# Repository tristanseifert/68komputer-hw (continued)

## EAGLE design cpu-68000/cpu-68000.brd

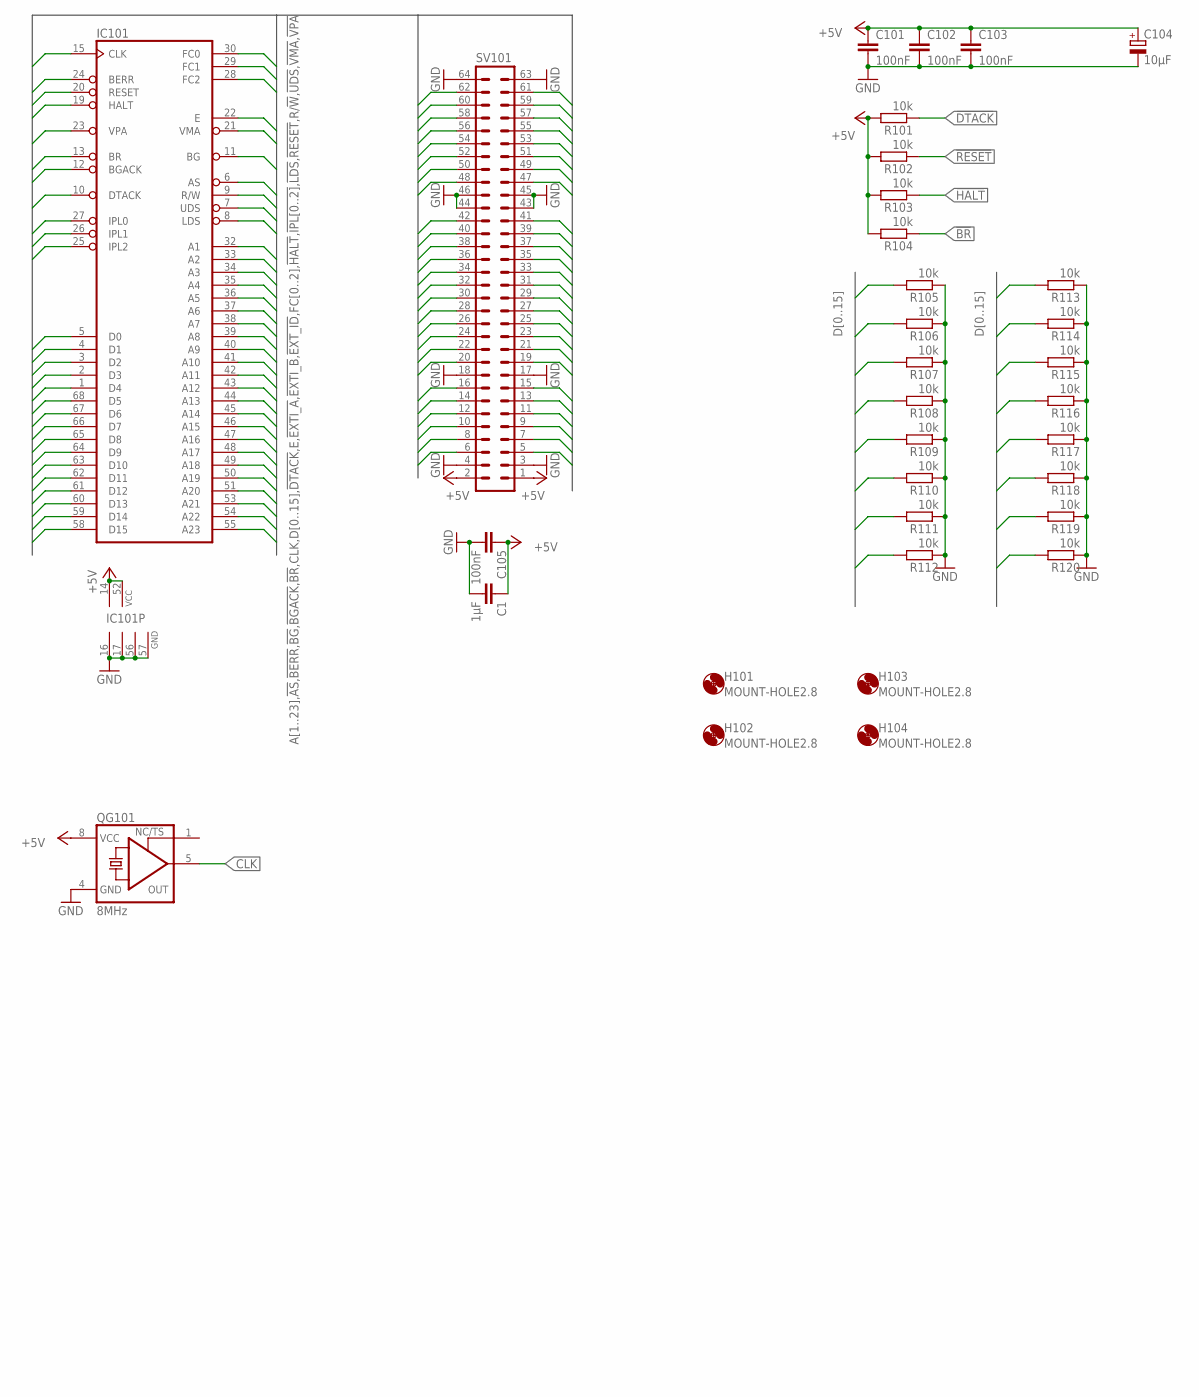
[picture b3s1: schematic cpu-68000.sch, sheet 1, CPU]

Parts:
C1: 1µF; C0805; MOUSER 710-885012207078
C101, C102, C103, C105: 100nF; C0805; MOUSER 710-885012207072
C104: 10µF; SMC_B; MOUSER 581-TAJB106K020RNJV
H101, H102, H103, H104: MOUNT-HOLE2.8; 2,8
IC101: MC68000FN-SOC; PLCC68SOCK; MOUSER_SOCKET 940-44-068-24-000000
QG101: 8MHz; DIL08S; MOUSER 774-MXO45HS-3C-8.0
R101, R102, R103, R104, R105, R106, R107, R108, R109, R110, R111, R112, R113, R114, R115, R116, R117, R118, R119, R120: 10k; R2012; MOUSER 652-CR0805FX-1002ELF
SV101: ML64L

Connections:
!AS: IC101.6 (AS), SV101.13; also elsewhere on the board
!BERR: IC101.24 (BERR); also elsewhere on the board
!BG: IC101.11 (BG), SV101.9
!BGACK: IC101.12 (BGACK), SV101.8
!BR: IC101.13 (BR), R104.1, SV101.7
!DTACK: IC101.10 (DTACK), R101.1, SV101.10; also elsewhere on the board
!EXTI_A: SV101.16; also elsewhere on the board
!EXTI_B: SV101.15; also elsewhere on the board
!EXT_ID: SV101.41; also elsewhere on the board
!HALT: IC101.19 (HALT), R103.1, SV101.5; also elsewhere on the board
!IPL0: IC101.27 (IPL0); also elsewhere on the board
!IPL1: IC101.26 (IPL1); also elsewhere on the board
!IPL2: IC101.25 (IPL2); also elsewhere on the board
!LDS: IC101.8 (LDS), SV101.11; also elsewhere on the board
!RESET: IC101.20 (RESET), R102.1, SV101.6; also elsewhere on the board
!UDS: IC101.7 (UDS), SV101.14; also elsewhere on the board
!VMA: IC101.21 (VMA)
!VPA: IC101.23 (VPA); also elsewhere on the board
+5V: C1.1, C101.1, C102.1, C103.1, C104.+, C105.1, IC101.14 (VCC), IC101.52 (VCC), QG101.8 (VCC), R101.2, R102.2, R103.2, R104.2, SV101.1, SV101.2; also elsewhere on the board
A1: IC101.32 (A1), SV101.20; also elsewhere on the board
A2: IC101.33 (A2), SV101.22; also elsewhere on the board
A3: IC101.34 (A3), SV101.19; also elsewhere on the board
A4: IC101.35 (A4), SV101.24; also elsewhere on the board
A5: IC101.36 (A5), SV101.21; also elsewhere on the board
A6: IC101.37 (A6), SV101.23; also elsewhere on the board
A7: IC101.38 (A7), SV101.26; also elsewhere on the board
A8: IC101.39 (A8), SV101.25; also elsewhere on the board
A9: IC101.40 (A9), SV101.28; also elsewhere on the board
A10: IC101.41 (A10), SV101.27; also elsewhere on the board
A11: IC101.42 (A11), SV101.30; also elsewhere on the board
A12: IC101.43 (A12), SV101.29; also elsewhere on the board
A13: IC101.44 (A13), SV101.31; also elsewhere on the board
A14: IC101.45 (A14), SV101.32; also elsewhere on the board
A15: IC101.46 (A15), SV101.33; also elsewhere on the board
A16: IC101.47 (A16), SV101.34; also elsewhere on the board
A17: IC101.48 (A17), SV101.36; also elsewhere on the board
A18: IC101.49 (A18), SV101.35; also elsewhere on the board
A19: IC101.50 (A19), SV101.38; also elsewhere on the board
A20: IC101.51 (A20), SV101.37; also elsewhere on the board
A21: IC101.53 (A21), SV101.40; also elsewhere on the board
A22: IC101.54 (A22), SV101.39; also elsewhere on the board
A23: IC101.55 (A23), SV101.42; also elsewhere on the board
CLK: IC101.15 (CLK), QG101.5 (OUT); also elsewhere on the board
D0: IC101.5 (D0), R105.2, SV101.62; also elsewhere on the board
D1: IC101.4 (D1), R106.2, SV101.60; also elsewhere on the board
D2: IC101.3 (D2), R107.2, SV101.58; also elsewhere on the board
D3: IC101.2 (D3), R108.2, SV101.56; also elsewhere on the board
D4: IC101.1 (D4), R109.2, SV101.54; also elsewhere on the board
D5: IC101.68 (D5), R110.2, SV101.52; also elsewhere on the board
D6: IC101.67 (D6), R111.2, SV101.50; also elsewhere on the board
D7: IC101.66 (D7), R112.2, SV101.48; also elsewhere on the board
D8: IC101.65 (D8), R113.2, SV101.57; also elsewhere on the board
D9: IC101.64 (D9), R114.2, SV101.59; also elsewhere on the board
D10: IC101.63 (D10), R115.2, SV101.61; also elsewhere on the board
D11: IC101.62 (D11), R116.2, SV101.55; also elsewhere on the board
D12: IC101.61 (D12), R117.2, SV101.53; also elsewhere on the board
D13: IC101.60 (D13), R118.2, SV101.51; also elsewhere on the board
D14: IC101.59 (D14), R119.2, SV101.49; also elsewhere on the board
D15: IC101.58 (D15), R120.2, SV101.47; also elsewhere on the board
E: IC101.22 (E); also elsewhere on the board
FC0: IC101.30 (FC0); also elsewhere on the board
FC1: IC101.29 (FC1); also elsewhere on the board
FC2: IC101.28 (FC2); also elsewhere on the board
GND: C1.2, C101.2, C102.2, C103.2, C104.-, C105.2, IC101.16 (GND), IC101.17 (GND), IC101.56 (GND), IC101.57 (GND), QG101.4 (GND), R105.1, R106.1, R107.1, R108.1, R109.1, R110.1, R111.1, R112.1, R113.1, R114.1, R115.1, R116.1, R117.1, R118.1, R119.1, R120.1, SV101.3, SV101.4, SV101.17, SV101.18, SV101.43, SV101.44, SV101.45, SV101.46, SV101.63, SV101.64; also elsewhere on the board
R/!W!: IC101.9 (R/W), SV101.12; also elsewhere on the board

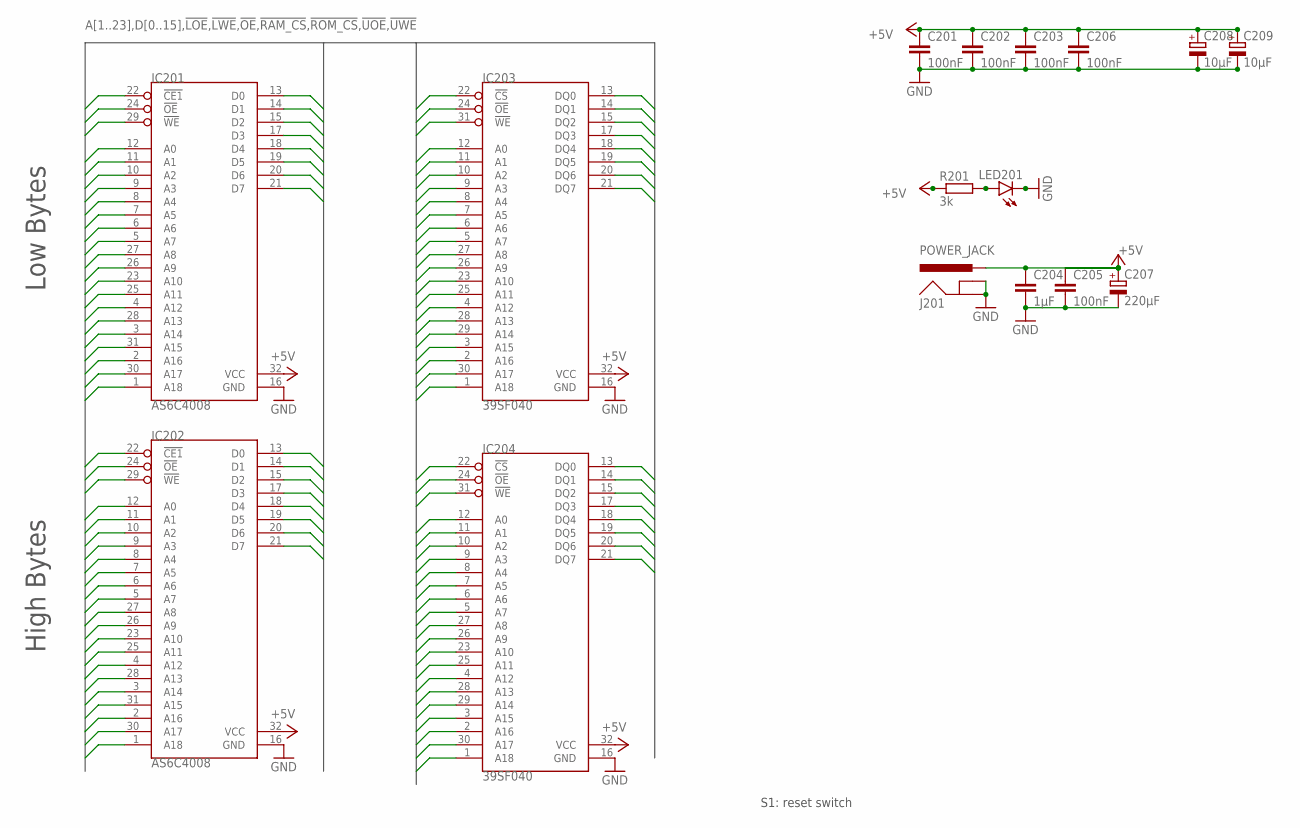
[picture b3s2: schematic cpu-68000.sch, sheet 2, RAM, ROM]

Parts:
C201, C202, C203, C205, C206: 100nF; C0805; MOUSER 710-885012207072
C204: 1µF; C0805; MOUSER 710-885012107015
C207: 220µF; E2,5-7; MOUSER 710-860020373010
C208, C209: 10µF; SMC_B; MOUSER 581-TAJB106K020RNJV
IC201, IC202: AS6C4008; DIL32; MOUSER_SOCKET 575-1144632
IC203, IC204: 39SF040; DIL32; MOUSER 804-39SF0407CPHE
J201: POWER_JACK; POWER_JACK_PTH
LED201: LEDCHIPLED_1206; CHIPLED_1206; MOUSER 710-156120YS75300
R201: 3k; R2012; MOUSER 652-CR0805JW-302ELF

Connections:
!LOE: IC201.24 (!OE), IC203.24 (!OE); also elsewhere on the board
!LWE: IC201.29 (!WE), IC203.31 (!WE); also elsewhere on the board
!RAM_CS: IC201.22 (!CE1), IC202.22 (!CE1); also elsewhere on the board
!ROM_CS: IC203.22 (!CS), IC204.22 (!CS); also elsewhere on the board
!UOE: IC202.24 (!OE), IC204.24 (!OE); also elsewhere on the board
!UWE: IC202.29 (!WE), IC204.31 (!WE); also elsewhere on the board
+5V: C201.1, C202.1, C203.1, C204.1, C205.1, C206.1, C207.+, C208.+, C209.+, IC201.32 (VCC), IC202.32 (VCC), IC203.32 (VCC), IC204.32 (VCC), J201.PWR, R201.1; also elsewhere on the board
A1: IC201.12 (A0), IC202.12 (A0), IC203.12 (A0), IC204.12 (A0); also elsewhere on the board
A2: IC201.11 (A1), IC202.11 (A1), IC203.11 (A1), IC204.11 (A1); also elsewhere on the board
A3: IC201.10 (A2), IC202.10 (A2), IC203.10 (A2), IC204.10 (A2); also elsewhere on the board
A4: IC201.9 (A3), IC202.9 (A3), IC203.9 (A3), IC204.9 (A3); also elsewhere on the board
A5: IC201.8 (A4), IC202.8 (A4), IC203.8 (A4), IC204.8 (A4); also elsewhere on the board
A6: IC201.7 (A5), IC202.7 (A5), IC203.7 (A5), IC204.7 (A5); also elsewhere on the board
A7: IC201.6 (A6), IC202.6 (A6), IC203.6 (A6), IC204.6 (A6); also elsewhere on the board
A8: IC201.5 (A7), IC202.5 (A7), IC203.5 (A7), IC204.5 (A7); also elsewhere on the board
A9: IC201.27 (A8), IC202.27 (A8), IC203.27 (A8), IC204.27 (A8); also elsewhere on the board
A10: IC201.26 (A9), IC202.26 (A9), IC203.26 (A9), IC204.26 (A9); also elsewhere on the board
A11: IC201.23 (A10), IC202.23 (A10), IC203.23 (A10), IC204.23 (A10); also elsewhere on the board
A12: IC201.25 (A11), IC202.25 (A11), IC203.25 (A11), IC204.25 (A11); also elsewhere on the board
A13: IC201.4 (A12), IC202.4 (A12), IC203.4 (A12), IC204.4 (A12); also elsewhere on the board
A14: IC201.28 (A13), IC202.28 (A13), IC203.28 (A13), IC204.28 (A13); also elsewhere on the board
A15: IC201.3 (A14), IC202.3 (A14), IC203.29 (A14), IC204.29 (A14); also elsewhere on the board
A16: IC201.31 (A15), IC202.31 (A15), IC203.3 (A15), IC204.3 (A15); also elsewhere on the board
A17: IC201.2 (A16), IC202.2 (A16), IC203.2 (A16), IC204.2 (A16); also elsewhere on the board
A18: IC201.30 (A17), IC202.30 (A17), IC203.30 (A17), IC204.30 (A17); also elsewhere on the board
A19: IC201.1 (A18), IC202.1 (A18), IC203.1 (A18), IC204.1 (A18); also elsewhere on the board
D0: IC201.13 (D0), IC203.13 (DQ0); also elsewhere on the board
D1: IC201.14 (D1), IC203.14 (DQ1); also elsewhere on the board
D2: IC201.15 (D2), IC203.15 (DQ2); also elsewhere on the board
D3: IC201.17 (D3), IC203.17 (DQ3); also elsewhere on the board
D4: IC201.18 (D4), IC203.18 (DQ4); also elsewhere on the board
D5: IC201.19 (D5), IC203.19 (DQ5); also elsewhere on the board
D6: IC201.20 (D6), IC203.20 (DQ6); also elsewhere on the board
D7: IC201.21 (D7), IC203.21 (DQ7); also elsewhere on the board
D8: IC202.13 (D0), IC204.13 (DQ0); also elsewhere on the board
D9: IC202.14 (D1), IC204.14 (DQ1); also elsewhere on the board
D10: IC202.15 (D2), IC204.15 (DQ2); also elsewhere on the board
D11: IC202.17 (D3), IC204.17 (DQ3); also elsewhere on the board
D12: IC202.18 (D4), IC204.18 (DQ4); also elsewhere on the board
D13: IC202.19 (D5), IC204.19 (DQ5); also elsewhere on the board
D14: IC202.20 (D6), IC204.20 (DQ6); also elsewhere on the board
D15: IC202.21 (D7), IC204.21 (DQ7); also elsewhere on the board
GND: C201.2, C202.2, C203.2, C204.2, C205.2, C206.2, C207.-, C208.-, C209.-, IC201.16 (GND), IC202.16 (GND), IC203.16 (GND), IC204.16 (GND), J201.GND, J201.GNDBREAK, LED201.C; also elsewhere on the board
unnamed: LED201.A, R201.2

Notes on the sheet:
S1: reset switch
Low Bytes
High Bytes

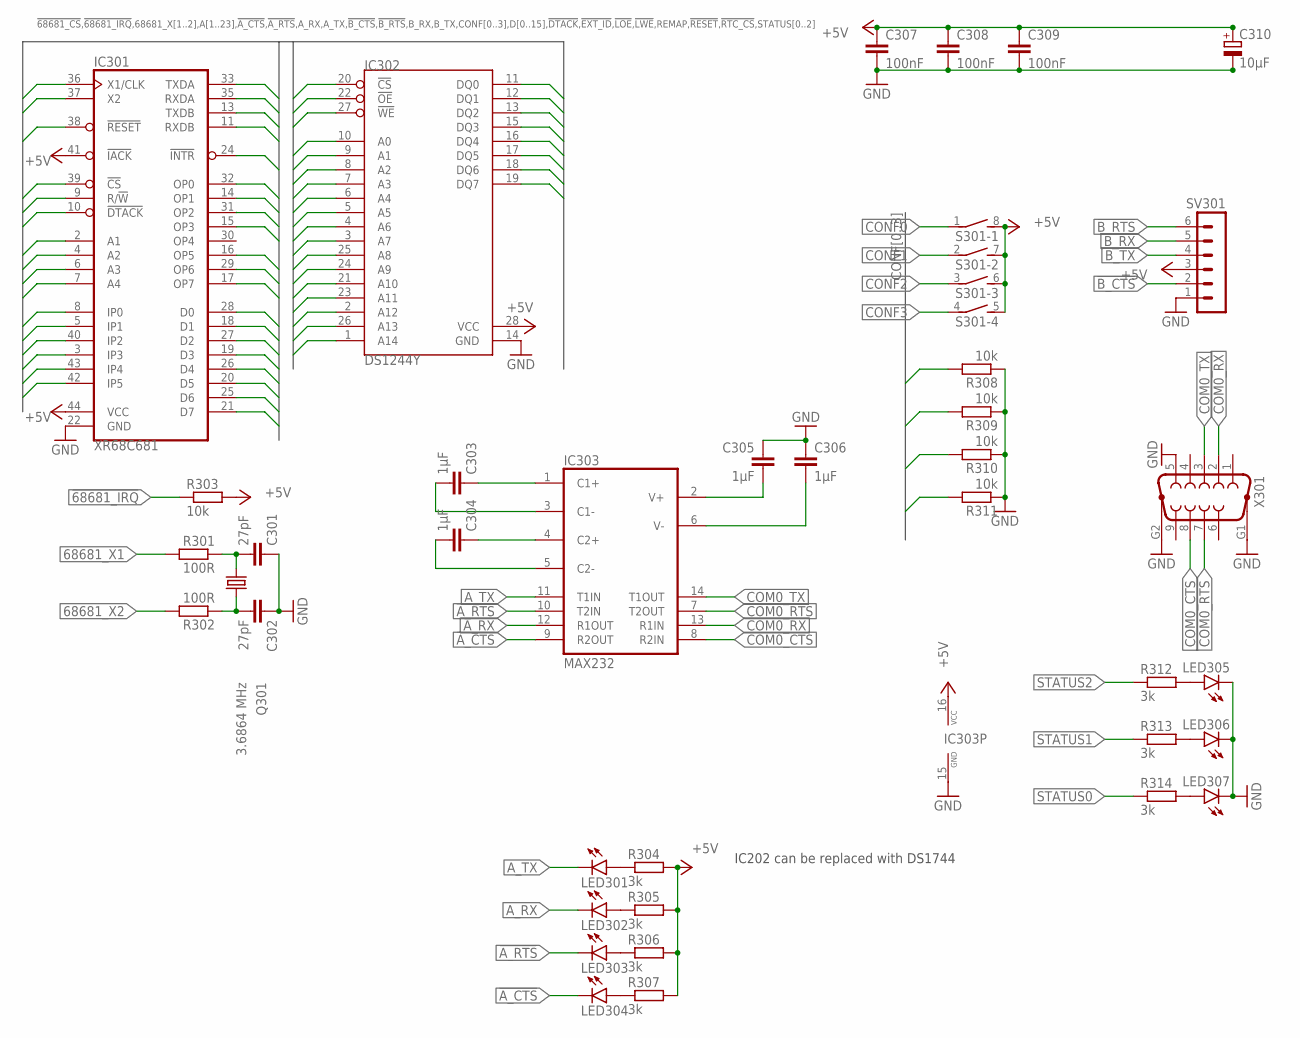
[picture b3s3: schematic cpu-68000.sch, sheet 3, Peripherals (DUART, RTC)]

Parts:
C301, C302: 27pF; C0805; MOUSER 80-C0805C270K5HACTU
C303, C304, C305, C306: 1µF; C0805; MOUSER 710-885012207078
C307, C308, C309: 100nF; C0805; MOUSER 710-885012207072
C310: 10µF; SMC_B; MOUSER 581-TAJB106K020RNJV
IC301: XR68C681; PLCC-S44; MOUSER 701-XR68C681CJ-F
IC302: DS1244Y; DIL28-6; MOUSER_SOCKET 575-1104762841001000
IC303: MAX232; DIL16; MOUSER 595-MAX232ECN
LED301, LED302, LED303, LED304, LED305, LED306, LED307: LEDCHIPLED_1206; CHIPLED_1206; MOUSER 710-156120VS75300
Q301: 3.6864 MHz; HC49/S; MOUSER 815-ABL-3.6864-B2
R301, R302: 100R; R2012; MOUSER 652-CR0805FX-1000ELF
R303, R308, R309, R310, R311: 10k; R2012; MOUSER 652-CR0805FX-1002ELF
R304, R305, R306, R307, R312, R313, R314: 3k; R2012; MOUSER 652-CR0805JW-302ELF
S301: DIP04S; MOUSER 653-A6FR-4104
SV301: MA06-1
X301: F09HP; MOUSER 806-K22X-E9P-N-99

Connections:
68681_X1: IC301.36 (X1/CLK), R301.2
68681_X2: IC301.37 (X2), R302.2
!68681_CS: IC301.39 (!CS); also elsewhere on the board
!68681_IRQ: IC301.24 (!INTR), R303.1; also elsewhere on the board
!A_CTS: IC301.8 (IP0), IC303.9 (R2OUT), LED304.C
!A_RTS: IC301.32 (OP0), IC303.10 (T2IN), LED303.C
!B_CTS: IC301.5 (IP1), SV301.2
!B_RTS: IC301.14 (OP1), SV301.6
!DTACK: IC301.10 (!DTACK); also elsewhere on the board
!EXT_ID: IC301.29 (OP6); also elsewhere on the board
!LOE: IC302.22 (!OE); also elsewhere on the board
!LWE: IC301.9 (R/!W), IC302.27 (!WE); also elsewhere on the board
!RESET: IC301.38 (!RESET); also elsewhere on the board
!RTC_CS: IC302.20 (!CS); also elsewhere on the board
+5V: C307.1, C308.1, C309.1, C310.+, IC301.41 (!IACK), IC301.44 (VCC), IC302.28 (VCC), IC303.16 (VCC), R303.2, R304.2, R305.2, R306.2, R307.2, S301.5 (2), S301.6 (2), S301.7 (2), S301.8 (2), SV301.3; also elsewhere on the board
A1: IC301.2 (A1), IC302.10 (A0); also elsewhere on the board
A2: IC301.4 (A2), IC302.9 (A1); also elsewhere on the board
A3: IC301.6 (A3), IC302.8 (A2); also elsewhere on the board
A4: IC301.7 (A4), IC302.7 (A3); also elsewhere on the board
A5: IC302.6 (A4); also elsewhere on the board
A6: IC302.5 (A5); also elsewhere on the board
A7: IC302.4 (A6); also elsewhere on the board
A8: IC302.3 (A7); also elsewhere on the board
A9: IC302.25 (A8); also elsewhere on the board
A10: IC302.24 (A9); also elsewhere on the board
A11: IC302.21 (A10); also elsewhere on the board
A12: IC302.23 (A11); also elsewhere on the board
A13: IC302.2 (A12); also elsewhere on the board
A14: IC302.26 (A13); also elsewhere on the board
A15: IC302.1 (A14); also elsewhere on the board
A_RX: IC301.35 (RXDA), IC303.12 (R1OUT), LED302.C
A_TX: IC301.33 (TXDA), IC303.11 (T1IN), LED301.C
B_RX: IC301.11 (RXDB), SV301.5
B_TX: IC301.13 (TXDB), SV301.4
COM0_CTS: IC303.8 (R2IN), X301.8
COM0_RTS: IC303.7 (T2OUT), X301.7
COM0_RX: IC303.13 (R1IN), X301.2
COM0_TX: IC303.14 (T1OUT), X301.3
CONF0: IC301.40 (IP2), R308.2, S301.1
CONF1: IC301.43 (IP4), R309.2, S301.2 (1)
CONF2: IC301.42 (IP5), R310.2, S301.3 (1)
CONF3: IC301.3 (IP3), R311.2, S301.4 (1)
D0: IC301.28 (D0), IC302.11 (DQ0); also elsewhere on the board
D1: IC301.18 (D1), IC302.12 (DQ1); also elsewhere on the board
D2: IC301.27 (D2), IC302.13 (DQ2); also elsewhere on the board
D3: IC301.19 (D3), IC302.15 (DQ3); also elsewhere on the board
D4: IC301.26 (D4), IC302.16 (DQ4); also elsewhere on the board
D5: IC301.20 (D5), IC302.17 (DQ5); also elsewhere on the board
D6: IC301.25 (D6), IC302.18 (DQ6); also elsewhere on the board
D7: IC301.21 (D7), IC302.19 (DQ7); also elsewhere on the board
GND: C301.1, C302.1, C305.1, C306.1, C307.2, C308.2, C309.2, C310.-, IC301.22 (GND), IC302.14 (GND), IC303.15 (GND), LED305.C, LED306.C, LED307.C, R308.1, R309.1, R310.1, R311.1, SV301.1, X301.5, X301.G1, X301.G2; also elsewhere on the board
unnamed: C305.2, IC303.2 (V+)
unnamed: C301.2, Q301.1, R301.1
unnamed: C302.2, Q301.2, R302.1
unnamed: LED306.A, R313.2
unnamed: LED307.A, R314.2
unnamed: LED305.A, R312.2
unnamed: LED301.A, R304.1
unnamed: LED302.A, R305.1
unnamed: LED303.A, R306.1
unnamed: LED304.A, R307.1
unnamed: C306.2, IC303.6 (V-)
unnamed: C304.1, IC303.4 (C2+)
unnamed: C303.1, IC303.1 (C1+)
unnamed: C303.2, IC303.3 (C1-)
unnamed: C304.2, IC303.5 (C2-)
REMAP: IC301.31 (OP2); also elsewhere on the board
STATUS0: IC301.16 (OP5), R314.1
STATUS1: IC301.17 (OP7), R313.1
STATUS2: IC301.15 (OP3), R312.1

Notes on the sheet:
IC202 can be replaced with DS1744

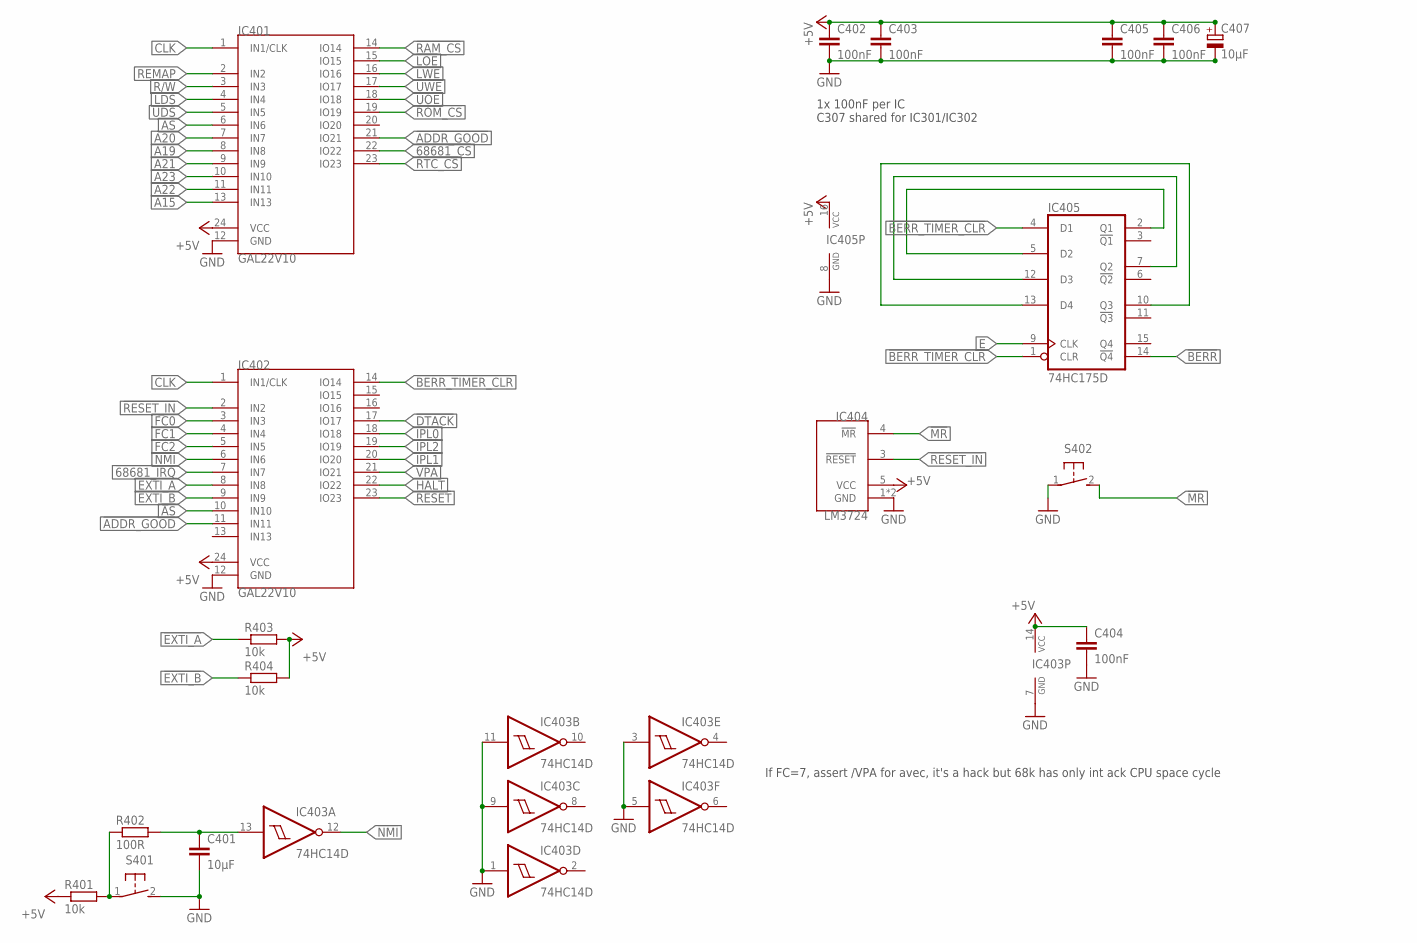
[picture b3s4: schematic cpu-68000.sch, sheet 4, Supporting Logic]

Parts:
C401: 10µF; C0805; MOUSER 791-0805F106Z100CT
C402, C403, C404, C405, C406: 100nF; C0805; MOUSER 710-885012207072
C407: 10µF; SMC_B; MOUSER 581-TAJB106K020RNJV
IC401, IC402: GAL22V10; DIL24S; MOUSER_SOCKET 575-1104732441001000
IC403: 74HC14D; SO14; MOUSER 771-74HC14D-T
IC404: LM3724; SOT23-5
IC405: 74HC175D; SO16; MOUSER 595-CD74HCT175M
R401, R403, R404: 10k; R2012; MOUSER 652-CR0805FX-1002ELF
R402: 100R; R2012; MOUSER 652-CR0805JW-101ELF
S401, S402: 31-XX; B3F-31XX; MOUSER 653-B3F-3150

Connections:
!68681_CS: IC401.22 (IO22); also elsewhere on the board
!68681_IRQ: IC402.7 (IN7); also elsewhere on the board
!ADDR_GOOD: IC401.21 (IO21), IC402.11 (IN11)
!AS: IC401.6 (IN6), IC402.10 (IN10); also elsewhere on the board
!BERR: IC405.14 (!Q4); also elsewhere on the board
!BERR_TIMER_CLR: IC402.14 (IO14), IC405.1 (CLR), IC405.4 (D1)
!DTACK: IC402.17 (IO17); also elsewhere on the board
!EXTI_A: IC402.8 (IN8), R403.1; also elsewhere on the board
!EXTI_B: IC402.9 (IN9), R404.1; also elsewhere on the board
!HALT: IC402.22 (IO22); also elsewhere on the board
!IPL0: IC402.18 (IO18); also elsewhere on the board
!IPL1: IC402.20 (IO20); also elsewhere on the board
!IPL2: IC402.19 (IO19); also elsewhere on the board
!LDS: IC401.4 (IN4); also elsewhere on the board
!LOE: IC401.15 (IO15); also elsewhere on the board
!LWE: IC401.16 (IO16); also elsewhere on the board
!MR: IC404.4 (!MR), S402.2 (S)
!NMI: IC402.6 (IN6), IC403.12 (O)
!RAM_CS: IC401.14 (IO14); also elsewhere on the board
!RESET: IC402.23 (IO23); also elsewhere on the board
!RESET_IN: IC402.2 (IN2), IC404.3 (!RESET)
!ROM_CS: IC401.19 (IO19); also elsewhere on the board
!RTC_CS: IC401.23 (IO23); also elsewhere on the board
!UDS: IC401.5 (IN5); also elsewhere on the board
!UOE: IC401.18 (IO18); also elsewhere on the board
!UWE: IC401.17 (IO17); also elsewhere on the board
!VPA: IC402.21 (IO21); also elsewhere on the board
+5V: C402.1, C403.1, C404.1, C405.1, C406.1, C407.+, IC401.24 (VCC), IC402.24 (VCC), IC403.14 (VCC), IC404.5 (VCC), IC405.16 (VCC), R401.1, R403.2, R404.2; also elsewhere on the board
A15: IC401.13 (IN13); also elsewhere on the board
A19: IC401.8 (IN8); also elsewhere on the board
A20: IC401.7 (IN7); also elsewhere on the board
A21: IC401.9 (IN9); also elsewhere on the board
A22: IC401.11 (IN11); also elsewhere on the board
A23: IC401.10 (IN10); also elsewhere on the board
CLK: IC401.1 (IN1/CLK), IC402.1 (IN1/CLK); also elsewhere on the board
E: IC405.9 (CLK); also elsewhere on the board
FC0: IC402.3 (IN3); also elsewhere on the board
FC1: IC402.4 (IN4); also elsewhere on the board
FC2: IC402.5 (IN5); also elsewhere on the board
GND: C401.2, C402.2, C403.2, C404.2, C405.2, C406.2, C407.-, IC401.12 (GND), IC402.12 (GND), IC403.1 (I), IC403.3 (I), IC403.5 (I), IC403.7 (GND), IC403.9 (I), IC403.11 (I), IC404.1 (GND), IC404.2 (GND), IC405.8 (GND), S401.2 (S), S402.1; also elsewhere on the board
unnamed: IC405.2 (Q1), IC405.5 (D2)
unnamed: IC405.7 (Q2), IC405.12 (D3)
unnamed: IC405.10 (Q3), IC405.13 (D4)
unnamed: R401.2, R402.1, S401.1
unnamed: C401.1, IC403.13 (I), R402.2
R/!W!: IC401.3 (IN3); also elsewhere on the board
REMAP: IC401.2 (IN2); also elsewhere on the board

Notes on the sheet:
1x 100nF per IC C307 shared for IC301/IC302
If FC=7, assert /VPA for avec, it's a hack but 68k has only int ack CPU space cycle

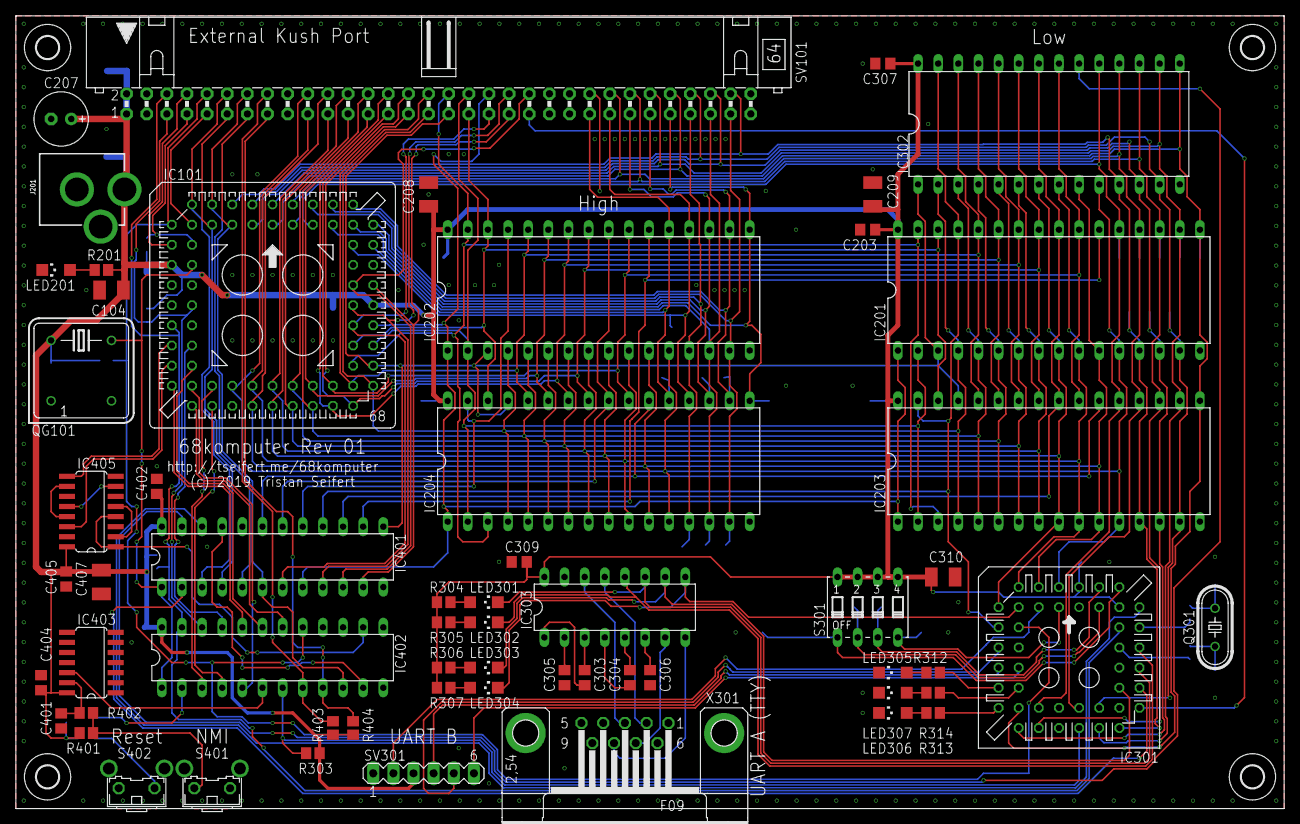
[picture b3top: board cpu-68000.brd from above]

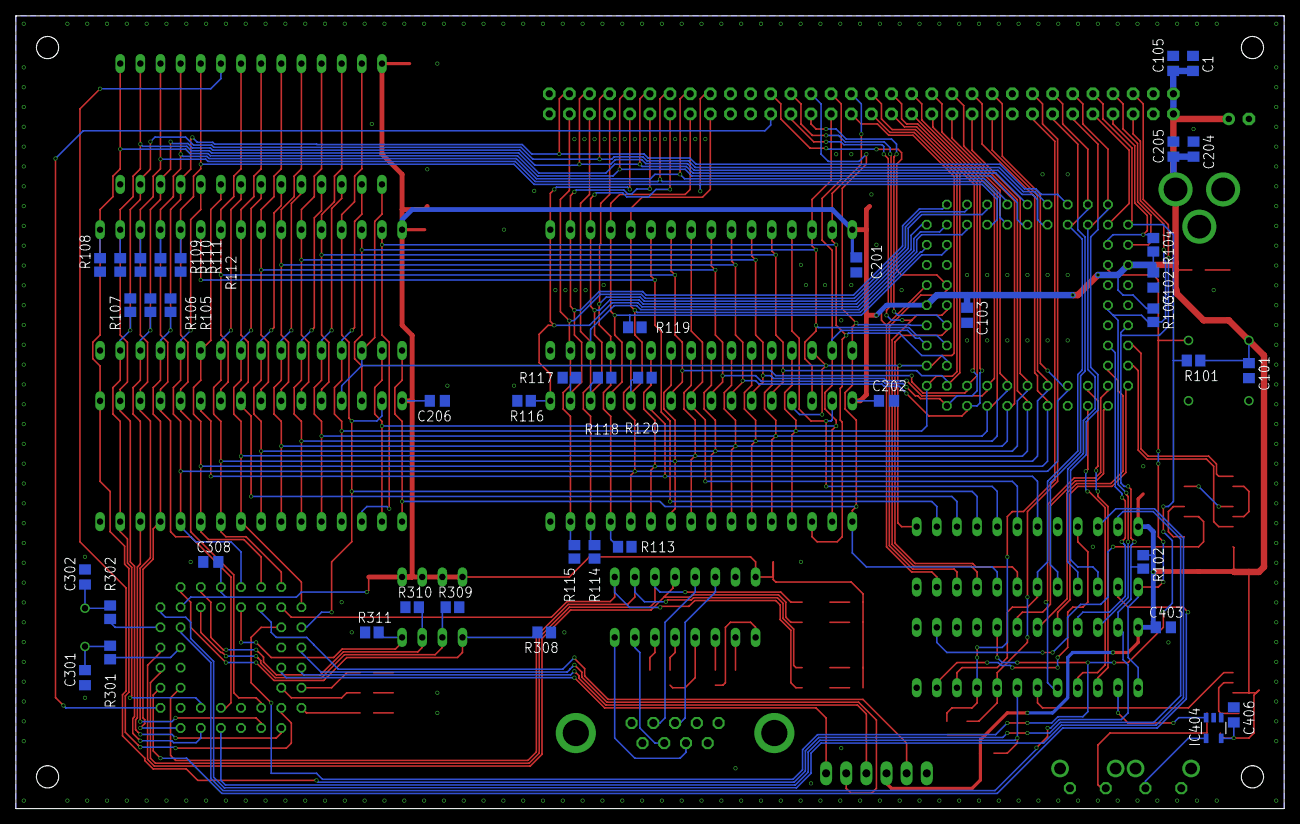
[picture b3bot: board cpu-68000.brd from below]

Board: 2 copper layers, 160.0 x 100.0 mm, 105 parts (42 on the bottom side), 121 nets.

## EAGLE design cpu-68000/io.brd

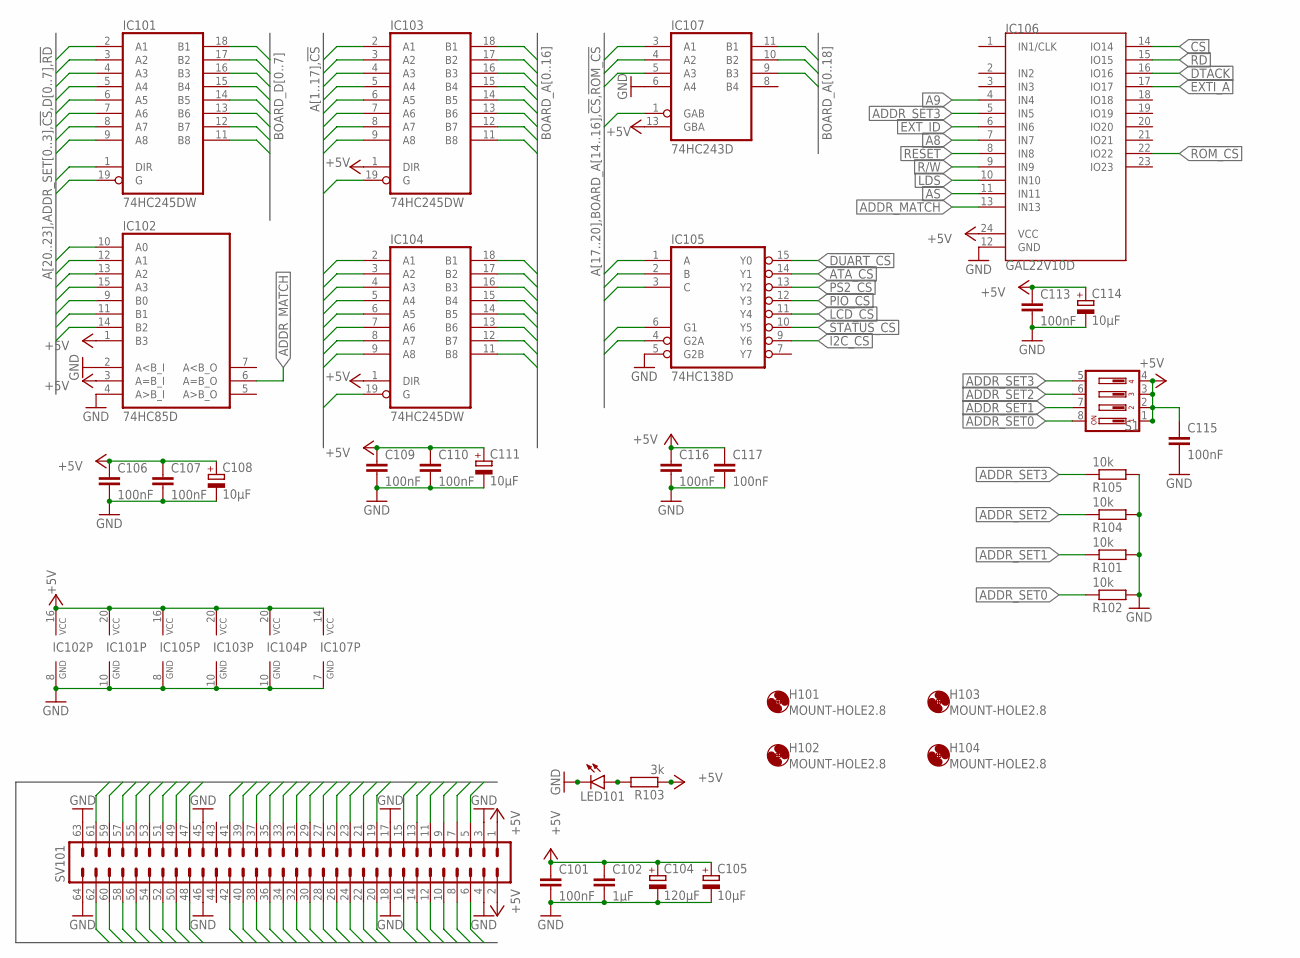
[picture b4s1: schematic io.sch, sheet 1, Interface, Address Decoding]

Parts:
C101, C106, C107, C109, C110, C113, C115, C116, C117: 100nF; C0805; MOUSER 710-885012207072
C102: 1µF; C0805; MOUSER 710-885012207078
C104: 120µF; E2,5-7; MOUSER 710-860020373007
C105, C108, C111, C114: 10µF; SMC_B; MOUSER 581-TAJB106K020RNJV
H101, H102, H103, H104: MOUNT-HOLE2.8; 2,8
IC101, IC103, IC104: 74HC245DW; SO20W; MOUSER 595-SN74HC245DWR
IC102: 74HC85D; SO16; MOUSER 771-74HC138D
IC105: 74HC138D; SO16; MOUSER 771-74HC138D
IC106: GAL22V10D; DIL24S; MOUSER_SOCKET 575-1104732441001000
IC107: 74HC243D; SO14; MOUSER 595-CD74HC243M96
LED101: LEDCHIPLED_1206; CHIPLED_1206; MOUSER 710-156120YS75300
R101, R102, R104, R105: 10k; R2012; MOUSER 652-CR0805FX-1002ELF
R103: 3k; R2012; MOUSER 652-CR0805JW-302ELF
S1: DP04; DP-04; MOUSER 653-A6FR-2104
SV101: ML64L

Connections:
!AS: IC106.11 (IN11), SV101.13
!ATA_CS: IC105.14 (Y1)
!BG: SV101.9
!BGACK: SV101.8
!BR: SV101.7
!CS: IC101.19 (G), IC103.19 (G), IC104.19 (G), IC105.4 (G2A), IC106.14 (IO14), IC107.1 (GAB)
!DTACK: IC106.16 (IO16), SV101.10; also elsewhere on the board
!DUART_CS: IC105.15 (Y0); also elsewhere on the board
!EXTI_A: IC106.17 (IO17), SV101.16
!EXTI_B: SV101.15
!EXT_ID: IC106.6 (IN6), SV101.41
!HALT: SV101.5
!I2C_CS: IC105.9 (Y6)
!LCD_CS: IC105.11 (Y4)
!LDS: IC106.10 (IN10), SV101.11
!PIO_CS: IC105.12 (Y3)
!PS2_CS: IC105.13 (Y2); also elsewhere on the board
!RD: IC101.1 (DIR), IC106.15 (IO15); also elsewhere on the board
!RESET: IC106.8 (IN8), SV101.6; also elsewhere on the board
!ROM_CS: IC105.6 (G1), IC106.22 (IO22); also elsewhere on the board
!STATUS_CS: IC105.10 (Y5)
!UDS: SV101.14
+5V: C101.1, C102.1, C104.+, C105.+, C106.1, C107.1, C108.+, C109.1, C110.1, C111.+, C113.1, C114.+, C115.1, C116.1, C117.1, IC101.20 (VCC), IC102.1 (B3), IC102.3 (A=B_I), IC102.16 (VCC), IC103.1 (DIR), IC103.20 (VCC), IC104.1 (DIR), IC104.20 (VCC), IC105.16 (VCC), IC106.24 (VCC), IC107.13 (GBA), IC107.14 (VCC), R103.1, S1.1, S1.2, S1.3, S1.4, SV101.1, SV101.2; also elsewhere on the board
A1: IC103.2 (A1), SV101.20
A2: IC103.3 (A2), SV101.22
A3: IC103.4 (A3), SV101.19
A4: IC103.5 (A4), SV101.24
A5: IC103.6 (A5), SV101.21
A6: IC103.7 (A6), SV101.23
A7: IC103.8 (A7), SV101.26
A8: IC103.9 (A8), IC106.7 (IN7), SV101.25
A9: IC104.2 (A1), IC106.4 (IN4), SV101.28
A10: IC104.3 (A2), SV101.27
A11: IC104.4 (A3), SV101.30
A12: IC104.5 (A4), SV101.29
A13: IC104.6 (A5), SV101.31
A14: IC104.7 (A6), SV101.32
A15: IC104.8 (A7), SV101.33
A16: IC104.9 (A8), SV101.34
A17: IC107.3 (A1), SV101.36
A18: IC107.4 (A2), SV101.35
A19: IC107.5 (A3), SV101.38
A20: IC102.10 (A0), SV101.37
A21: IC102.12 (A1), SV101.40
A22: IC102.13 (A2), SV101.39
A23: IC102.15 (A3), SV101.42
ADDR_MATCH: IC102.6 (A=B_O), IC106.13 (IN13)
ADDR_SET0: IC102.9 (B0), R102.1, S1.8
ADDR_SET1: IC102.11 (B1), R101.1, S1.7
ADDR_SET2: IC102.14 (B2), R104.1, S1.6
ADDR_SET3: IC106.5 (IN5), R105.1, S1.5
BOARD_A0: IC103.18 (B1); also elsewhere on the board
BOARD_A1: IC103.17 (B2); also elsewhere on the board
BOARD_A2: IC103.16 (B3); also elsewhere on the board
BOARD_A3: IC103.15 (B4); also elsewhere on the board
BOARD_A4: IC103.14 (B5); also elsewhere on the board
BOARD_A5: IC103.13 (B6); also elsewhere on the board
BOARD_A6: IC103.12 (B7); also elsewhere on the board
BOARD_A7: IC103.11 (B8); also elsewhere on the board
BOARD_A8: IC104.18 (B1); also elsewhere on the board
BOARD_A9: IC104.17 (B2); also elsewhere on the board
BOARD_A10: IC104.16 (B3); also elsewhere on the board
BOARD_A11: IC104.15 (B4); also elsewhere on the board
BOARD_A12: IC104.14 (B5); also elsewhere on the board
BOARD_A13: IC104.13 (B6); also elsewhere on the board
BOARD_A14: IC104.12 (B7), IC105.1 (A); also elsewhere on the board
BOARD_A15: IC104.11 (B8), IC105.2 (B); also elsewhere on the board
BOARD_A16: IC105.3 (C), IC107.11 (B1)
BOARD_A17: IC107.10 (B2)
BOARD_A18: IC107.9 (B3)
BOARD_D0: IC101.18 (B1); also elsewhere on the board
BOARD_D1: IC101.17 (B2); also elsewhere on the board
BOARD_D2: IC101.16 (B3); also elsewhere on the board
BOARD_D3: IC101.15 (B4); also elsewhere on the board
BOARD_D4: IC101.14 (B5); also elsewhere on the board
BOARD_D5: IC101.13 (B6); also elsewhere on the board
BOARD_D6: IC101.12 (B7); also elsewhere on the board
BOARD_D7: IC101.11 (B8); also elsewhere on the board
D0: IC101.2 (A1), SV101.62
D1: IC101.3 (A2), SV101.60
D2: IC101.4 (A3), SV101.58
D3: IC101.5 (A4), SV101.56
D4: IC101.6 (A5), SV101.54
D5: IC101.7 (A6), SV101.52
D6: IC101.8 (A7), SV101.50
D7: IC101.9 (A8), SV101.48
D8: SV101.57
D9: SV101.59
D10: SV101.61
D11: SV101.55
D12: SV101.53
D13: SV101.51
D14: SV101.49
D15: SV101.47
GND: C101.2, C102.2, C104.-, C105.-, C106.2, C107.2, C108.-, C109.2, C110.2, C111.-, C113.2, C114.-, C115.2, C116.2, C117.2, IC101.10 (GND), IC102.2 (A<B_I), IC102.4 (A>B_I), IC102.8 (GND), IC103.10 (GND), IC104.10 (GND), IC105.5 (G2B), IC105.8 (GND), IC106.12 (GND), IC107.6 (A4), IC107.7 (GND), LED101.C, R101.2, R102.2, R104.2, R105.2, SV101.3, SV101.4, SV101.17, SV101.18, SV101.45, SV101.46, SV101.63, SV101.64; also elsewhere on the board
unnamed: LED101.A, R103.2
R/!W!: IC106.9 (IN9), SV101.12; also elsewhere on the board
